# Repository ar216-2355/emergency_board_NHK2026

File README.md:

- 最大定常電流４０Aの電源基板（Emergency Board）
- リレーにケープルを直付けすることを想定
- 非常停止ボタンを２個搭載できる（一個のみ載せる場合は使わない端子を短絡）
- リレーのコイル間電圧を出力する端子がある

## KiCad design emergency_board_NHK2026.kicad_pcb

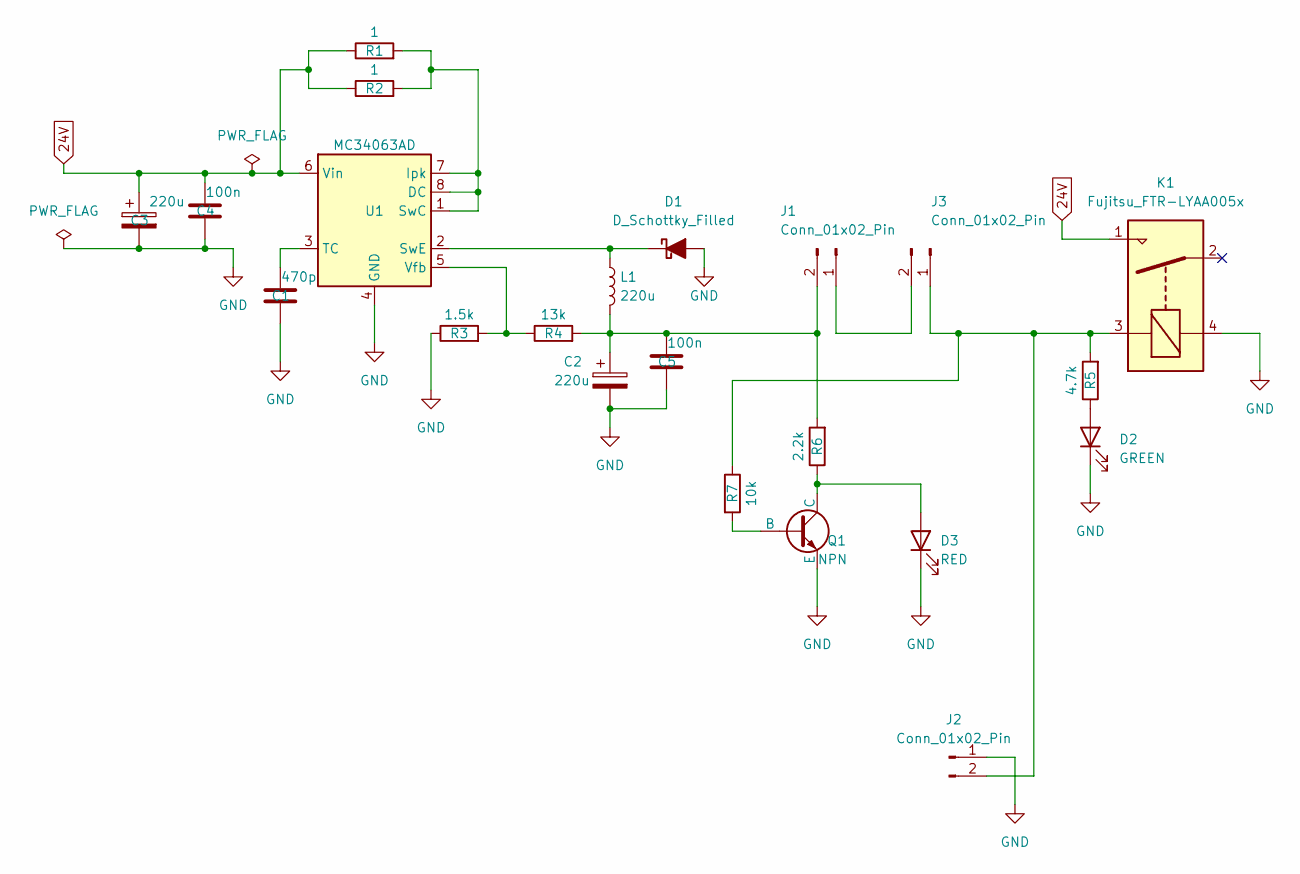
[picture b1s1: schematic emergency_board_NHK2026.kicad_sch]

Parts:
C1: 470p; C_0603_1608Metric
C2, C3: 220u; C_Radial_D8.0mm_H7.0mm_P3.50mm
C4, C5: 100n; C_0603_1608Metric
D1: D_Schottky_Filled; DIOM5227X270N
D2: GREEN; LED_0805_2012Metric
D3: RED; LED_0805_2012Metric
J1, J2, J3: Conn_01x02_Pin; JST_XH_B2B-XH-A_1x02_P2.50mm_Vertical
K1: Fujitsu_FTR-LYAA005x; relay_897_1AH_C_001
L1: 220u; my_L_1
Q1: NPN; SOT95P240X120-3N
R1, R2: 1; R_0603_1608Metric
R3: 1.5k; R_0603_1608Metric
R4: 13k; R_0603_1608Metric
R5: 4.7k; R_0603_1608Metric
R6: 2.2k; R_0603_1608Metric
R7: 10k; R_0603_1608Metric
U1: MC34063AD; SOIC-8_3.9x4.9mm_P1.27mm

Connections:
24V: C3.1, C4.1, K1.1, R1.1, R2.1, U1.6 (Vin)
GND: C1.2, C2.2, C3.2, C4.2, C5.2, D1.2 (A), D2.1 (K), D3.1 (K), J2.1, K1.4, Q1.3 (E), R3.1, U1.4 (GND)
unnamed: D1.1 (K), L1.1, U1.2 (SwE)
unnamed: D2.2 (A), R5.1
unnamed: D3.2 (A), Q1.1 (C), R6.1
unnamed: J1.1, J3.2
unnamed: C2.1, C5.1, J1.2, L1.2, R4.2, R6.2
unnamed: J2.2, J3.1, K1.3, R5.2, R7.1
unnamed: Q1.2 (B), R7.2
unnamed: R1.2, R2.2, U1.1 (SwC), U1.7 (Ipk), U1.8 (DC)
unnamed: C1.1, U1.3 (TC)
unnamed: R3.2, R4.1, U1.5 (Vfb)

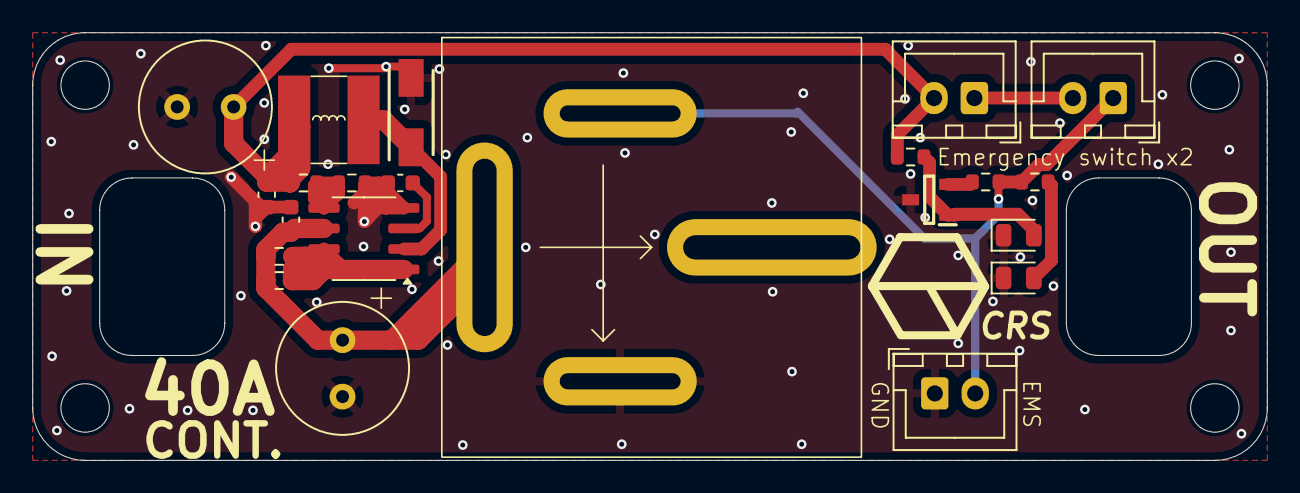
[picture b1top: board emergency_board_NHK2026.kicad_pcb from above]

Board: 2 copper layers, 76.5 x 26.5 mm, 22 parts (0 on the bottom side), 12 nets.

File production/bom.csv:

Designator,Footprint,Quantity,Value,LCSC Part #
C1,0603,1,470p,
"C2, C3",C_Radial_D8.0mm_H7.0mm_P3.50mm,2,220u,
"C4, C5",0603,2,100n,
D1,DIOM5227X270N,1,D_Schottky_Filled,
D2,0805,1,GREEN,
D3,0805,1,RED,
"J1, J2, J3",JST_XH_B2B-XH-A_1x02_P2.50mm_Vertical,3,Conn_01x02_Pin,
K1,relay_897_1AH_C_001,1,Fujitsu_FTR-LYAA005x,
L1,my_L_1,1,220u,
Q1,SOT95P240X120-3N,1,NPN,
"R1, R2",0603,2,1,
R3,0603,1,1.5k,
R4,0603,1,13k,
R5,0603,1,4.7k,
R6,0603,1,2.2k,
R7,0603,1,10k,
U1,SOIC-8_3.9x4.9mm_P1.27mm,1,MC34063AD,

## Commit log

2026-01-07 readme
2026-01-07 readme2
